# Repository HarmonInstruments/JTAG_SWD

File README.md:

# JTAG_SWD

## JTAG

Hirose DF3A-6P-2DS header

## Adapter Cables

###

Hirose DF3-6EP-2C 6 pin inline header

TC2030-MCP
TC2030-MCP-NL

## Pinout

|Pin |JTAG | Serial Wire | AVR |
|----|-----|-------------|-----|
| 1  | VCC | VCC         | VCC |
| 2  | TCK | SWCLK       | SCK |
| 3  | GND | GND         | GND |
| 4  | TDO | SWDIO       | MISO |
| 5  | NC  | jumper to 6 | NC |
| 6  | NC  | jumper to 5 | NC |
| 7  | TDI | SWDIO       | MOSI |
| 8  | TMS | NC          | RST |

## OpenOCD config for ECP5-12

```
interface ftdi
ftdi_channel 0
ftdi_vid_pid 0x0403 0x6014
ftdi_layout_init 0x0058 0x00fb
ftdi_layout_signal nTRST -data 0x0010
ftdi_layout_signal nSRST -oe 0x0020
adapter_khz 10000

telnet_port 4444
gdb_port 3333
transport select jtag
reset_config none

jtag newtap lfe5 tap -expected-id 0x21111043 -irlen 8 -irmask 0xFF -ircapture 0x5
init
scan_chain
svf -tap lfe5.tap -quiet -progress build/display_fpga.svf
shutdown
```

## OpenOCD config for XC7A15T
```
interface ftdi
ftdi_channel 0
ftdi_vid_pid 0x0403 0x6014
ftdi_layout_init 0x0058 0x00fb
ftdi_layout_signal nTRST -data 0x0010
ftdi_layout_signal nSRST -oe 0x0020
telnet_port 4444
gdb_port 3333
transport select jtag
reset_config none
jtag newtap artix7 tap -irlen 6 -ignore-version -expected-id 0x0362E093
pld device virtex2 artix7.tap
adapter_khz 10000
adapter_nsrst_delay 200
init
pld load 0 top.bit
virtex2 read_stat 0
shutdown
```

## OpenOCD for SWD STM32F4

swd.cfg
```
source [find openocd.cfg]
flash info 0
flash write_image erase digital.elf
reset run
exit
```

openocd.cfg
```
interface ftdi
transport select swd
ftdi_channel 0
ftdi_vid_pid 0x0403 0x6014
ftdi_layout_init 0x0058 0x00fb
ftdi_layout_signal SWD_EN -data 0x0200
adapter_khz 1000
telnet_port 4444
gdb_port 3333
reset_config none
source [find target/stm32f4x.cfg]
init
reset halt
sleep 100
```

## AVRDude

```
avrdude -c c232hm -P USB -p m32u4 -v -b 500000
```

Higher baud rates failed.

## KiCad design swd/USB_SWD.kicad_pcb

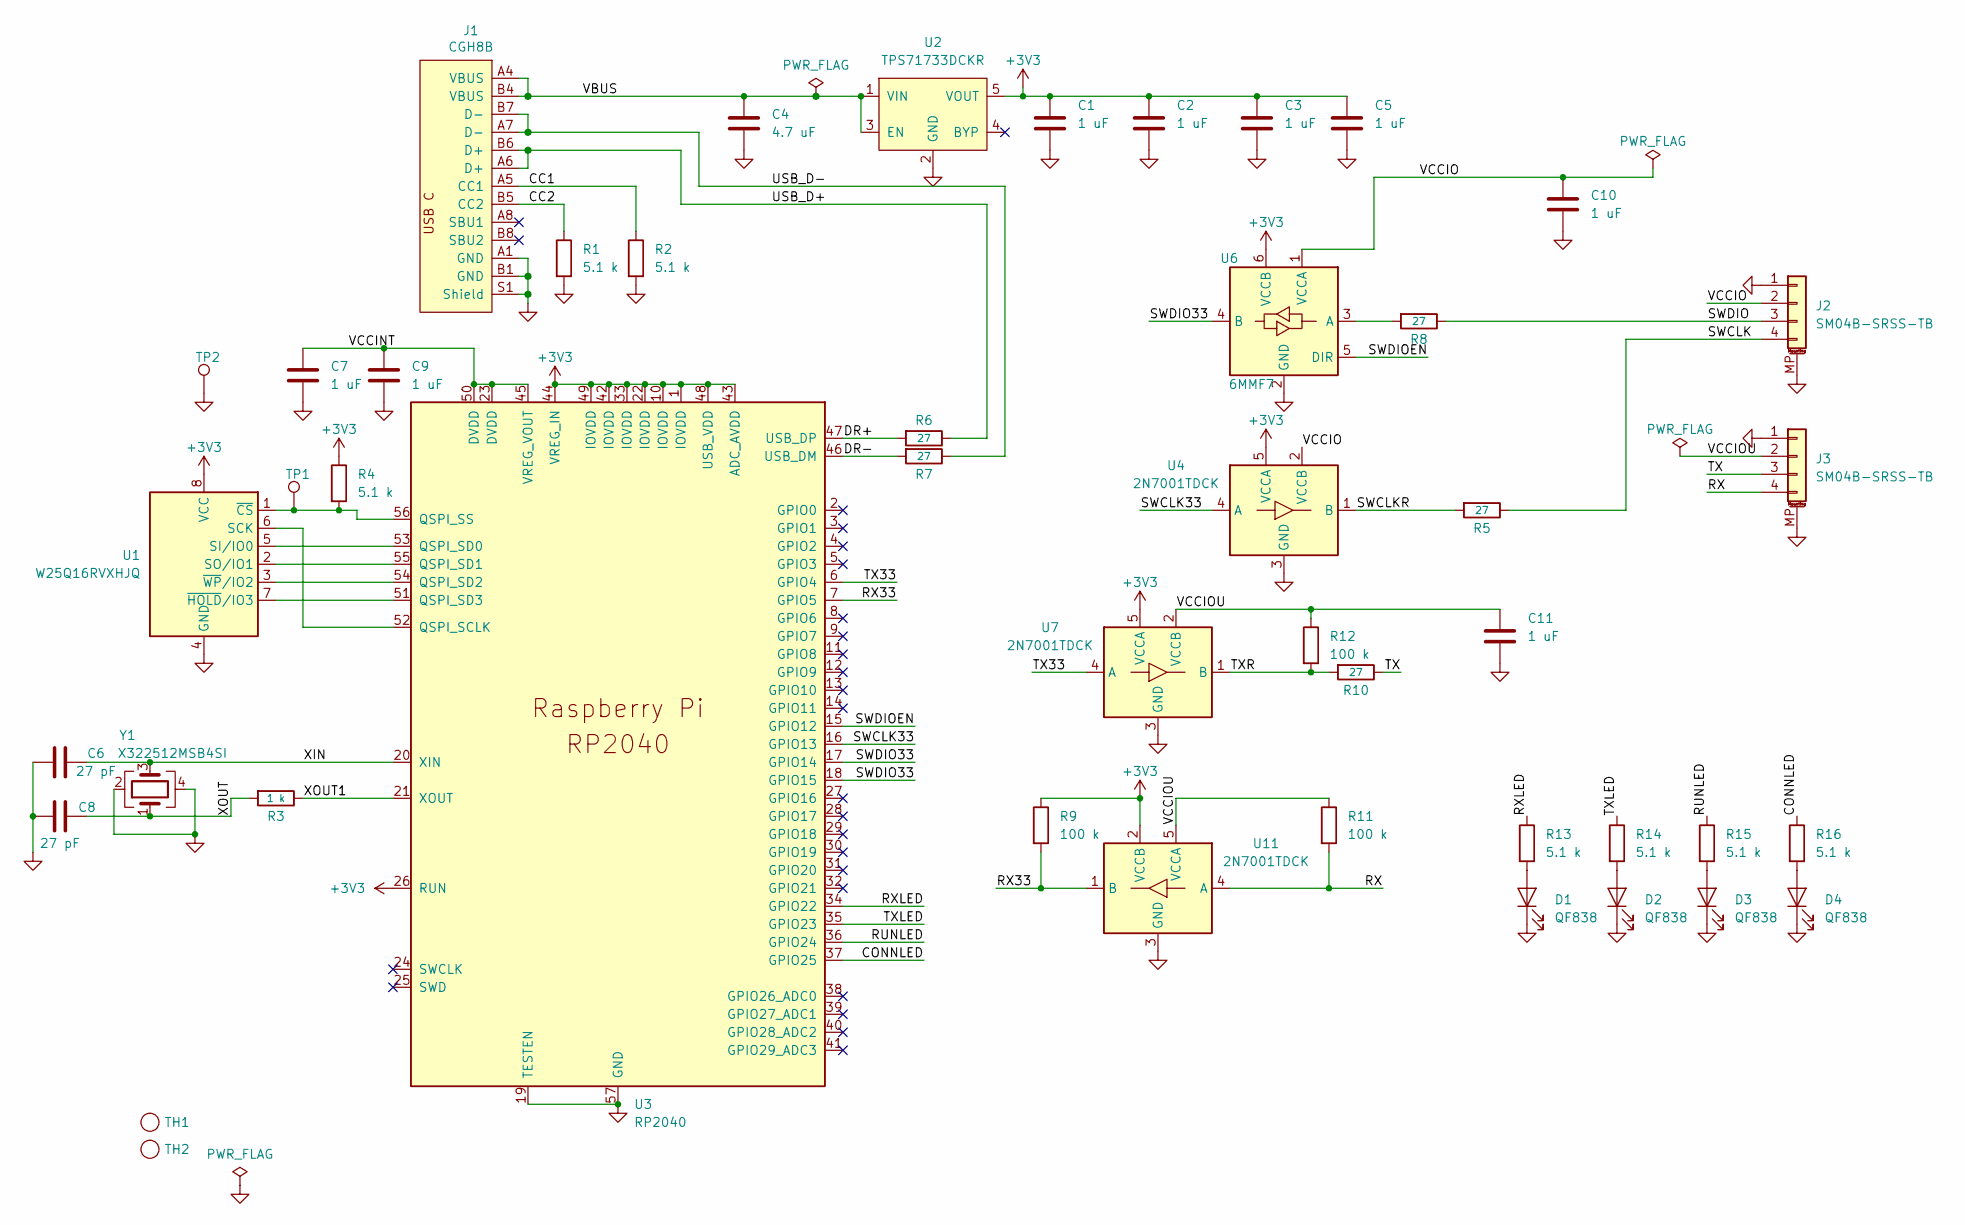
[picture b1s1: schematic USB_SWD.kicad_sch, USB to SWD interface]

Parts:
C1, C2, C3, C5, C7, C9, C10, C11: 1 uF; C_0402_1005Metric
C4: 4.7 uF; C_0603_1608Metric
C6, C8: 27 pF; C_0402_1005Metric
D1, D2, D3, D4: QF838; LED_0603_1608Metric
J1: CGH8B; USB_C_Receptacle_HRO_TYPE-C-31-M-12
J2, J3: SM04B-SRSS-TB; JST_SH_SM04B-SRSS-TB_1x04-1MP_P1.00mm_Horizontal
R1, R2, R4, R13, R14, R15, R16: 5.1 k; R_0402_1005Metric
R3: 1 k; R_0402_1005Metric
R5, R6, R7, R8, R10: 27; R_0402_1005Metric
R9, R11, R12: 100 k; R_0402_1005Metric
TH1, TH2: tooling_hole; tooling_hole_2.55
TP1, TP2: TestPoint; TestPoint_THTPad_1.5x1.5mm_Drill0.7mm
U1: W25Q16RVXHJQ; XSON-8-1EP_3x2mm_P0.5mm_EP0.2x1.6mm
U2: TPS71733DCKR; SOT-353_SC-70-5
U3: RP2040; QFN-56-RP2040
U4, U7, U11: 2N7001TDCK; SOT-353_SC-70-5
U6: 6MMF7; SOT-363_SC-70-6
Y1: X322512MSB4SI; Oscillator_SMD_SeikoEpson_SG8002CE-4Pin_3.2x2.5mm; LCSC C9002

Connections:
+3V3: C1.1, C2.1, C3.1, C5.1, R4.1, R9.1, U1.8 (VCC), U2.5 (VOUT), U3.1 (IOVDD), U3.10 (IOVDD), U3.22 (IOVDD), U3.26 (RUN), U3.33 (IOVDD), U3.42 (IOVDD), U3.43 (ADC_AVDD), U3.44 (VREG_IN), U3.48 (USB_VDD), U3.49 (IOVDD), U4.5 (VCCA), U6.6 (VCCB), U7.5 (VCCA), U11.2 (VCCB)
/CC1: J1.A5 (CC1), R2.1
/CC2: J1.B5 (CC2), R1.1
/CONNLED: R16.1, U3.37 (GPIO25)
/DR+: R6.2, U3.47 (USB_DP)
/DR-: R7.2, U3.46 (USB_DM)
/RUNLED: R15.1, U3.36 (GPIO24)
/RX: J3.4, R11.2, U11.4 (A)
/RX33: R9.2, U3.7 (GPIO5), U11.1 (B)
/RXLED: R13.1, U3.34 (GPIO22)
/SWCLK: J2.4, R5.1
/SWCLK33: U3.16 (GPIO13), U4.4 (A)
/SWCLKR: R5.2, U4.1 (B)
/SWDIO: J2.3, R8.1
/SWDIO33: U3.17 (GPIO14), U3.18 (GPIO15), U6.4 (B)
/SWDIOEN: U3.15 (GPIO12), U6.5 (DIR)
/TX: J3.3, R10.1
/TX33: U3.6 (GPIO4), U7.4 (A)
/TXLED: R14.1, U3.35 (GPIO23)
/TXR: R10.2, R12.2, U7.1 (B)
/USB_D+: J1.A6 (D+), J1.B6 (D+), R6.1
/USB_D-: J1.A7 (D-), J1.B7 (D-), R7.1
/VBUS: C4.1, J1.A4 (VBUS), J1.B4 (VBUS), U2.1 (VIN), U2.3 (EN)
/VCCINT: C7.1, C9.1, U3.23 (DVDD), U3.45 (VREG_VOUT), U3.50 (DVDD)
/VCCIO: C10.1, J2.2, U4.2 (VCCB), U6.1 (VCCA)
/VCCIOU: C11.1, J3.2, R11.1, R12.1, U7.2 (VCCB), U11.5 (VCCA)
/XIN: C6.1, U3.20 (XIN), Y1.3
/XOUT: C8.1, R3.2, Y1.1
/XOUT1: R3.1, U3.21 (XOUT)
GND: C1.2, C2.2, C3.2, C4.2, C5.2, C6.2, C7.2, C8.2, C9.2, C10.2, C11.2, D1.1 (K), D2.1 (K), D3.1 (K), D4.1 (K), J1.A1 (GND), J1.B1 (GND), J1.S1 (Shield), J2.1, J2.MP (MountPin), J3.1, J3.MP (MountPin), R1.2, R2.2, TP2.1, U1.4 (GND), U2.2 (GND), U3.19 (TESTEN), U3.57 (GND), U4.3 (GND), U6.2 (GND), U7.3 (GND), U11.3 (GND), Y1.2, Y1.4
unnamed: D1.2 (A), R13.2
unnamed: D2.2 (A), R14.2
unnamed: D3.2 (A), R15.2
unnamed: D4.2 (A), R16.2
unnamed: U1.6 (SCK), U3.52 (QSPI_SCLK)
unnamed: U1.5 (SI/IO0), U3.53 (QSPI_SD0)
unnamed: U1.2 (SO/IO1), U3.55 (QSPI_SD1)
unnamed: R4.2, TP1.1, U1.1 (~CS), U3.56 (QSPI_SS)
unnamed: U1.7 (~HOLD/IO3), U3.51 (QSPI_SD3)
unnamed: U1.3 (~WP/IO2), U3.54 (QSPI_SD2)
unnamed: R8.2, U6.3 (A)

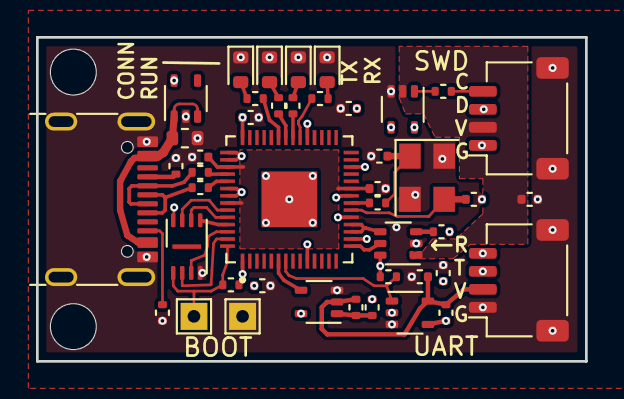
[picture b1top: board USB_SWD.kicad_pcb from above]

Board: 6 copper layers, 30.5 x 18.0 mm, 46 parts (0 on the bottom side), 41 nets.

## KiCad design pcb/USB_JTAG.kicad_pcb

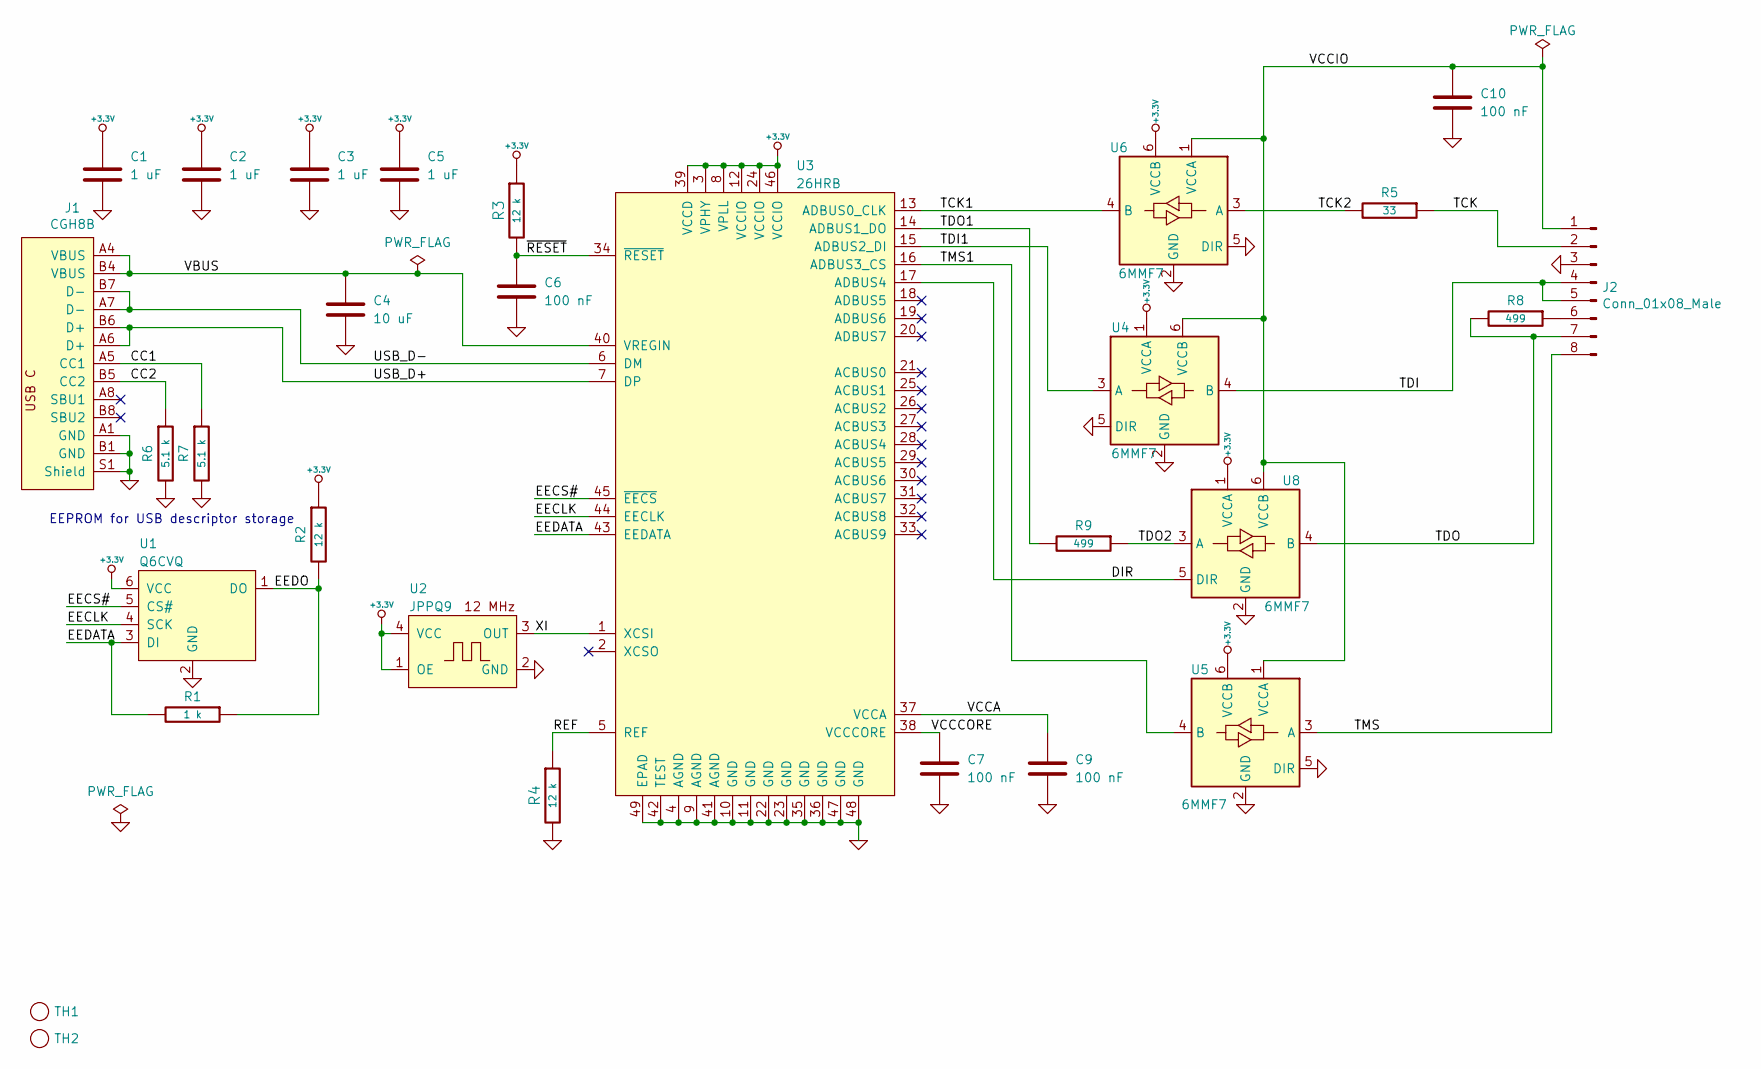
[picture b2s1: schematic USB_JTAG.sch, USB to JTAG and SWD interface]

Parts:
C1, C2, C3, C5: 1 uF; C_0402_1005Metric
C4: 10 uF; C_0805_2012Metric
C6, C7, C9, C10: 100 nF; C_0402_1005Metric
J1: CGH8B; USB_C_Receptacle_HRO_TYPE-C-31-M-12
J2: Conn_01x08_Male; Hirose_DF13-08P-1.25DSA_1x08_P1.25mm_Vertical
R1: 1 k; R_0402_1005Metric; Tolerance 10
R2, R3: 12 k; R_0402_1005Metric; Tolerance 10
R4: 12 k; R_0402_1005Metric; Tolerance 1
R5: 33; R_0402_1005Metric; Tolerance 10
R6, R7: 5.1 k; R_0402_1005Metric; Tolerance 10
R8, R9: 499; R_0402_1005Metric; Tolerance 10
TH1, TH2: tooling_hole; tooling_hole_2.55
U1: Q6CVQ; SOT-23-6
U2: JPPQ9; Oscillator_SMD_4Pin_2.5x2.0mm
U3: 26HRB; QFN-48-1EP_8x8mm_P0.5mm_EP6.2x6.2mm
U4, U5, U6, U8: 6MMF7; SOT-363_SC-70-6

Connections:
+3.3V: C1.1, C2.1, C3.1, C5.1, R2.1, R3.1, U1.6 (VCC), U2.1 (OE), U2.4 (VCC), U3.3 (VPHY), U3.8 (VPLL), U3.12 (VCCIO), U3.24 (VCCIO), U3.39 (VCCD), U3.46 (VCCIO), U4.1 (VCCA), U5.6 (VCCB), U6.6 (VCCB), U8.1 (VCCA)
/CC1: J1.A5 (CC1), R7.1
/CC2: J1.B5 (CC2), R6.1
/DIR: U3.17 (ADBUS4), U8.5 (DIR)
/EECLK: U1.4 (SCK), U3.44 (EECLK)
/EECS#: U1.5 (CS#), U3.45 (~EECS)
/EEDATA: R1.2, U1.3 (DI), U3.43 (EEDATA)
/EEDO: R1.1, R2.2, U1.1 (DO)
/REF: R4.1, U3.5 (REF)
/TCK: J2.2, R5.1
/TCK1: U3.13 (ADBUS0_CLK), U6.4 (B)
/TCK2: R5.2, U6.3 (A)
/TDI: J2.4, J2.5, U4.4 (B)
/TDI1: U3.15 (ADBUS2_DI), U4.3 (A)
/TDO: J2.7, R8.2, U8.4 (B)
/TDO1: R9.2, U3.14 (ADBUS1_DO)
/TDO2: R9.1, U8.3 (A)
/TMS: J2.8, U5.3 (A)
/TMS1: U3.16 (ADBUS3_CS), U5.4 (B)
/USB_D+: J1.A6 (D+), J1.B6 (D+), U3.7 (DP)
/USB_D-: J1.A7 (D-), J1.B7 (D-), U3.6 (DM)
/VBUS: C4.1, J1.A4 (VBUS), J1.B4 (VBUS), U3.40 (VREGIN)
/VCCA: C9.1, U3.37 (VCCA)
/VCCCORE: C7.1, U3.38 (VCCCORE)
/VCCIO: C10.1, J2.1, U4.6 (VCCB), U5.1 (VCCA), U6.1 (VCCA), U8.6 (VCCB)
/XI: U2.3 (OUT), U3.1 (XCSI)
/~RESET: C6.1, R3.2, U3.34 (~RESET)
GND: C1.2, C2.2, C3.2, C4.2, C5.2, C6.2, C7.2, C9.2, C10.2, J1.A1 (GND), J1.B1 (GND), J1.S1 (Shield), J2.3, R4.2, R6.2, R7.2, U1.2 (GND), U2.2 (GND), U3.4 (AGND), U3.9 (AGND), U3.10 (GND), U3.11 (GND), U3.22 (GND), U3.23 (GND), U3.35 (GND), U3.36 (GND), U3.41 (AGND), U3.42 (TEST), U3.47 (GND), U3.48 (GND), U3.49 (EPAD), U4.2 (GND), U4.5 (DIR), U5.2 (GND), U5.5 (DIR), U6.2 (GND), U6.5 (DIR), U8.2 (GND)
unnamed: J2.6, R8.1

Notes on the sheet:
EEPROM for USB descriptor storage

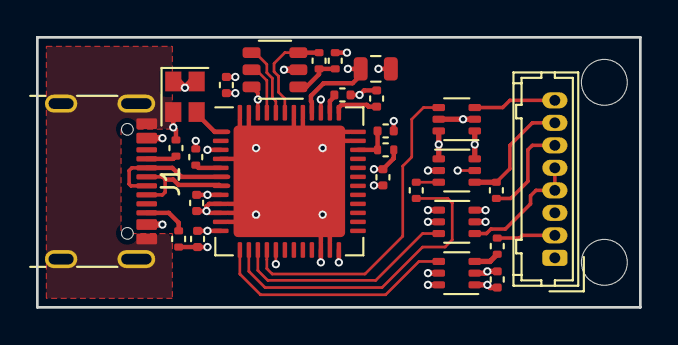
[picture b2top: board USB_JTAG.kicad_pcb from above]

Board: 4 copper layers, 33.5 x 15.0 mm, 29 parts (0 on the bottom side), 29 nets.

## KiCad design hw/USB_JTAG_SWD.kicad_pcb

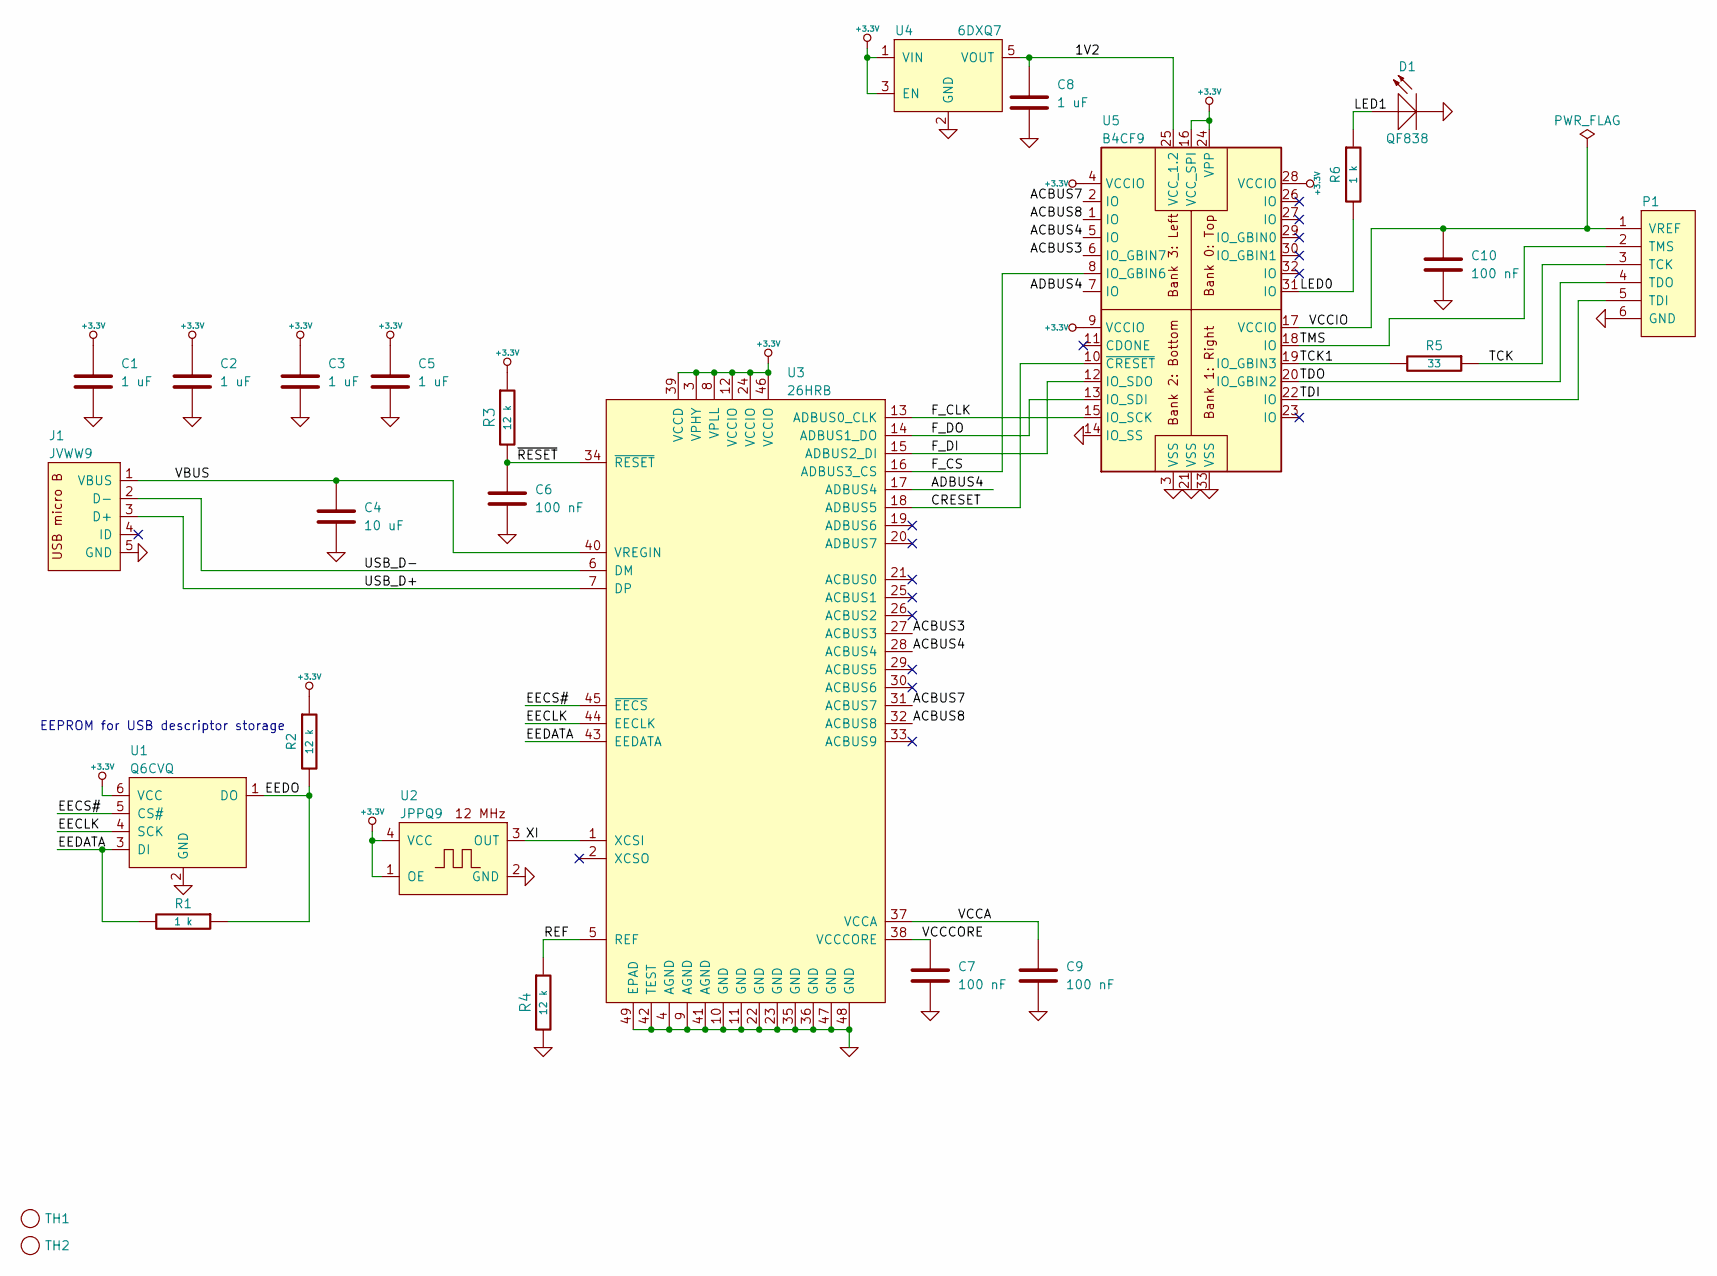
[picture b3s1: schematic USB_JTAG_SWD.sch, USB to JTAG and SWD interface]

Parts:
C1, C2, C3, C5, C8: 1 uF; 0402
C4: 10 uF; 0805
C6, C7, C9, C10: 100 nF; 0402
D1: QF838; 0603_led
J1: JVWW9; USB_micro_B
P1: DF3_6
R1, R6: 1 k; 0402_R; Tolerance 10
R2, R3: 12 k; 0402_R; Tolerance 10
R4: 12 k; 0402_R; Tolerance 1
R5: 33; 0402_R; Tolerance 10
TH1, TH2: tooling_hole; tooling_hole_2.55
U1: Q6CVQ; SOT23-6
U2: JPPQ9; osc_2.5x2
U3: 26HRB; QFN48_7x7
U4: 6DXQ7; SC70-5
U5: B4CF9; QFN32_5x5_4V

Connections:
+3.3V: C1.1, C2.1, C3.1, C5.1, R2.1, R3.1, U1.6 (VCC), U2.1 (OE), U2.4 (VCC), U3.3 (VPHY), U3.8 (VPLL), U3.12 (VCCIO), U3.24 (VCCIO), U3.39 (VCCD), U3.46 (VCCIO), U4.1 (VIN), U4.3 (EN), U5.4 (VCCIO), U5.9 (VCCIO), U5.16 (VCC_SPI), U5.24 (VPP), U5.28 (VCCIO)
/1V2: C8.1, U4.5 (VOUT), U5.25 (VCC_1.2)
/ACBUS3: U3.27 (ACBUS3), U5.6 (IO_GBIN7)
/ACBUS4: U3.28 (ACBUS4), U5.5 (IO)
/ACBUS7: U3.31 (ACBUS7), U5.2 (IO)
/ACBUS8: U3.32 (ACBUS8), U5.1 (IO)
/ADBUS4: U3.17 (ADBUS4), U5.7 (IO)
/CRESET: U3.18 (ADBUS5), U5.10 (~CRESET)
/EECLK: U1.4 (SCK), U3.44 (EECLK)
/EECS#: U1.5 (CS#), U3.45 (~EECS)
/EEDATA: R1.2, U1.3 (DI), U3.43 (EEDATA)
/EEDO: R1.1, R2.2, U1.1 (DO)
/F_CLK: U3.13 (ADBUS0_CLK), U5.15 (IO_SCK)
/F_CS: U3.16 (ADBUS3_CS), U5.8 (IO_GBIN6)
/F_DI: U3.15 (ADBUS2_DI), U5.12 (IO_SDO)
/F_DO: U3.14 (ADBUS1_DO), U5.13 (IO_SDI)
/LED0: R6.2, U5.31 (IO)
/LED1: D1.1 (A), R6.1
/REF: R4.1, U3.5 (REF)
/TCK: P1.3 (TCK), R5.1
/TCK1: R5.2, U5.19 (IO_GBIN3)
/TDI: P1.5 (TDI), U5.22 (IO)
/TDO: P1.4 (TDO), U5.20 (IO_GBIN2)
/TMS: P1.2 (TMS), U5.18 (IO)
/USB_D+: J1.3 (D+), U3.7 (DP)
/USB_D-: J1.2 (D-), U3.6 (DM)
/VBUS: C4.1, J1.1 (VBUS), U3.40 (VREGIN)
/VCCA: C9.1, U3.37 (VCCA)
/VCCCORE: C7.1, U3.38 (VCCCORE)
/VCCIO: C10.1, P1.1 (VREF), U5.17 (VCCIO)
/XI: U2.3 (OUT), U3.1 (XCSI)
/~RESET: C6.1, R3.2, U3.34 (~RESET)
GND: C1.2, C2.2, C3.2, C4.2, C5.2, C6.2, C7.2, C8.2, C9.2, C10.2, D1.2 (K), J1.5 (GND), P1.6 (GND), R4.2, U1.2 (GND), U2.2 (GND), U3.4 (AGND), U3.9 (AGND), U3.10 (GND), U3.11 (GND), U3.22 (GND), U3.23 (GND), U3.35 (GND), U3.36 (GND), U3.41 (AGND), U3.42 (TEST), U3.47 (GND), U3.48 (GND), U3.49 (EPAD), U4.2 (GND), U5.3 (VSS), U5.14 (IO_SS), U5.21 (VSS), U5.33 (VSS)

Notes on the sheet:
EEPROM for USB descriptor storage

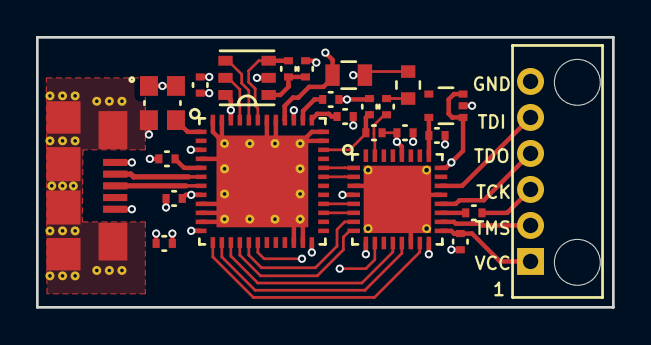
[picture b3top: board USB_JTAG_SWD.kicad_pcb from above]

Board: 4 copper layers, 32.0 x 15.0 mm, 26 parts (0 on the bottom side), 33 nets.

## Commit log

2018-10-16 initial import
2019-06-01 fix FT232 FP
2019-06-20 fix TDI/TDO swap closes #2
2019-08-16 add photo
2019-11-15 add pinout
2019-11-15 Fix net labels closes #3
2019-11-15 add openocd configs
2020-09-09 Add notes on using as an AVR programmer
2024-10-24 add SWD board

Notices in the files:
hw/USB_JTAG_SWD.sch:
Licensed under GNU GPL 3.0 or later
